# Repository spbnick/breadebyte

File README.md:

Breadebyte
==========

Breadebyte is a breakout board for EBYTE E73-2G4M08S1E module containing
Nordic nRF52833 SoC.

This uses a [shared symbol/footprint
library](https://github.com/spbnick/kicad-lib).

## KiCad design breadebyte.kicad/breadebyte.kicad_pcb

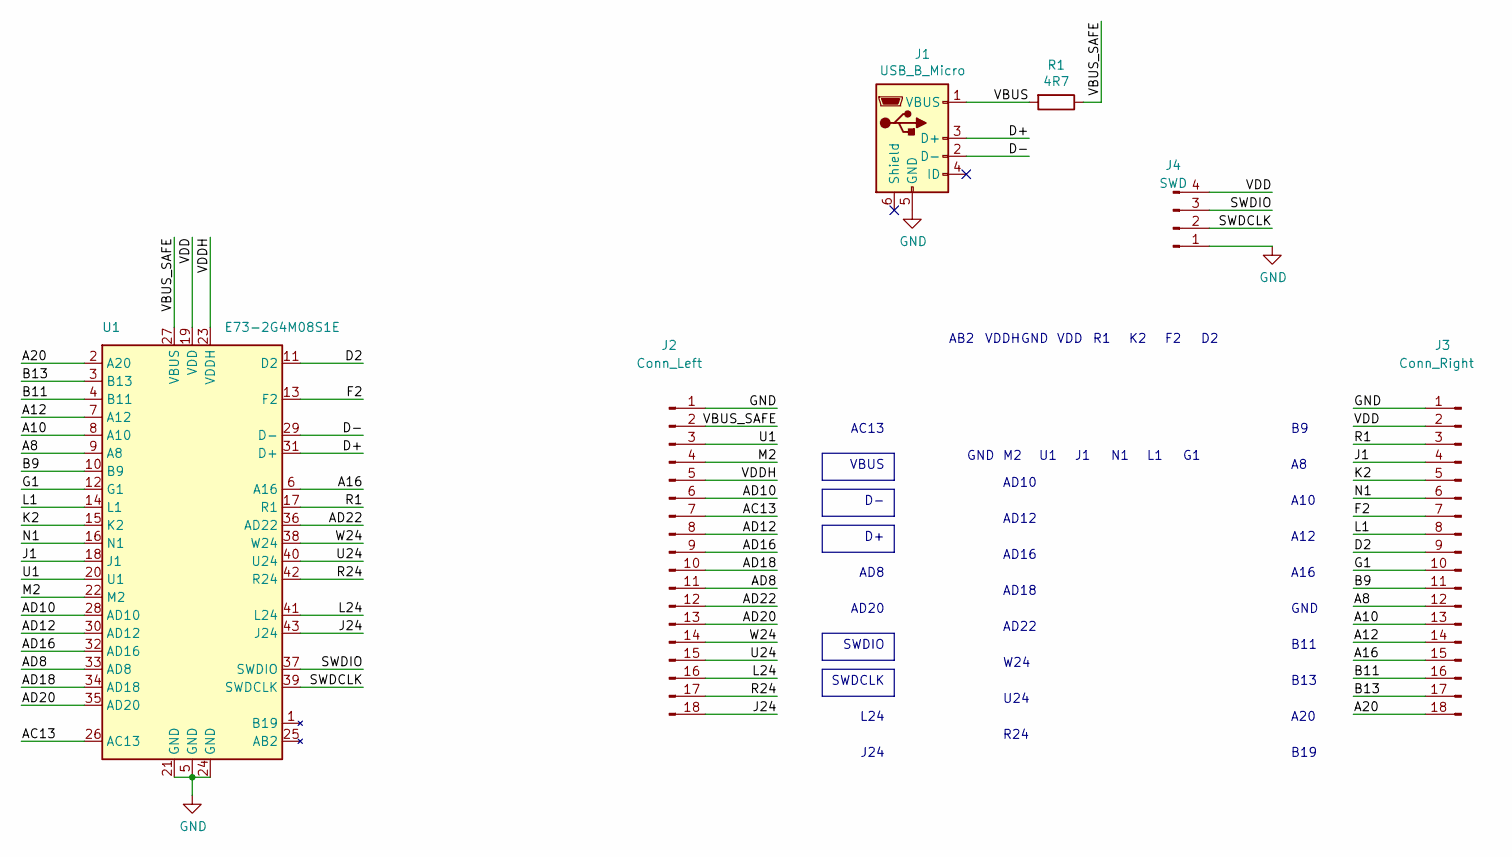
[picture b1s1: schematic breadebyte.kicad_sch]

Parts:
J1: USB_B_Micro; USB_Micro-B_HRO_U-D-M5DD-W-1_Vertical
J2: Conn_Left; PinHeader_1x18_P2.54mm_Vertical
J3: Conn_Right; PinHeader_1x18_P2.54mm_Vertical
J4: SWD; PinHeader_1x04_P2.54mm_Vertical
R1: 4R7; R_0805_2012Metric
U1: E73-2G4M08S1E

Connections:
/A8: J3.12, U1.9 (A8)
/A10: J3.13, U1.8 (A10)
/A12: J3.14, U1.7 (A12)
/A16: J3.15, U1.6 (A16)
/A20: J3.18, U1.2 (A20)
/AC13: J2.7, U1.26 (AC13)
/AD8: J2.11, U1.33 (AD8)
/AD10: J2.6, U1.28 (AD10)
/AD12: J2.8, U1.30 (AD12)
/AD16: J2.9, U1.32 (AD16)
/AD18: J2.10, U1.34 (AD18)
/AD20: J2.13, U1.35 (AD20)
/AD22: J2.12, U1.36 (AD22)
/B9: J3.11, U1.10 (B9)
/B11: J3.16, U1.4 (B11)
/B13: J3.17, U1.3 (B13)
/D2: J3.9, U1.11 (D2)
/D+: J1.3 (D+), U1.31 (D+)
/D-: J1.2 (D-), U1.29 (D-)
/F2: J3.7, U1.13 (F2)
/G1: J3.10, U1.12 (G1)
/J1: J3.4, U1.18 (J1)
/J24: J2.18, U1.43 (J24)
/K2: J3.5, U1.15 (K2)
/L1: J3.8, U1.14 (L1)
/L24: J2.16, U1.41 (L24)
/M2: J2.4, U1.22 (M2)
/N1: J3.6, U1.16 (N1)
/R1: J3.3, U1.17 (R1)
/R24: J2.17, U1.42 (R24)
/SWDCLK: J4.2, U1.39 (SWDCLK)
/SWDIO: J4.3, U1.37 (SWDIO)
/U1: J2.3, U1.20 (U1)
/U24: J2.15, U1.40 (U24)
/VBUS: J1.1 (VBUS), R1.2
/VBUS_SAFE: J2.2, R1.1, U1.27 (VBUS)
/VDD: J3.2, J4.4, U1.19 (VDD)
/VDDH: J2.5, U1.23 (VDDH)
/W24: J2.14, U1.38 (W24)
GND: J1.5 (GND), J2.1, J3.1, J4.1, U1.5 (GND), U1.21 (GND), U1.24 (GND)

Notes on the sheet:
B19
AB2
R24
AD22
VBUS
B13
A10
AD18
U24
GND
J24
SWDIO
L24
VDDH
SWDCLK
AD10
B11
AD12
AD8
A12
A20
A16
AD16
VDD
W24
AD20
AC13

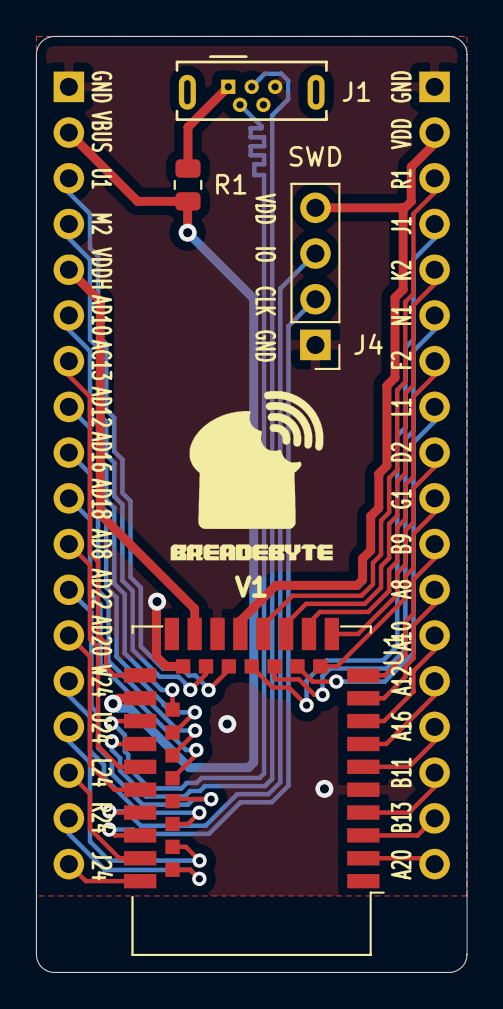
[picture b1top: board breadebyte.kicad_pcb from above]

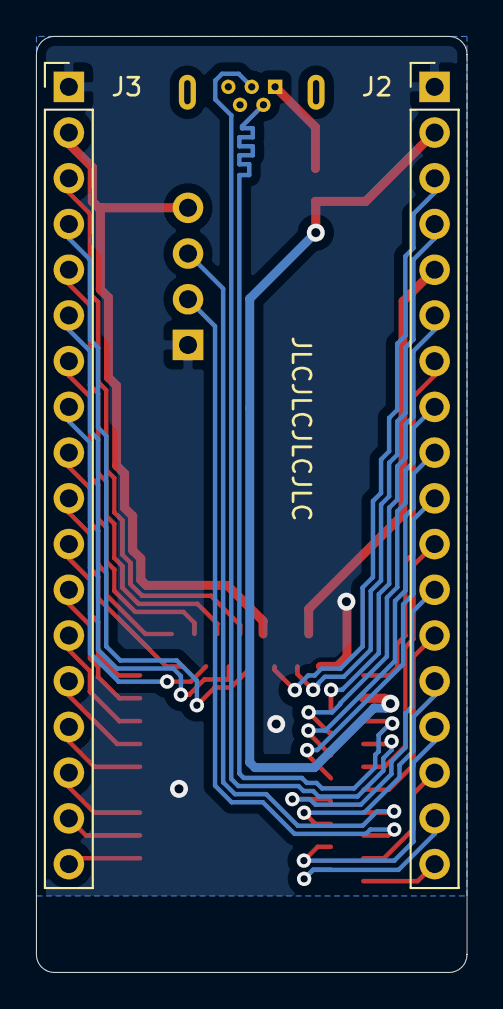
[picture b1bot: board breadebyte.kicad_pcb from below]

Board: 2 copper layers, 23.9 x 52.0 mm, 7 parts (2 on the bottom side), 40 nets.

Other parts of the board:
Ref**: Val**; logo

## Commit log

2022-01-22 Add v1 design
2022-01-22 Add a README.md with a photo
2022-04-23 Upgrade KiCAD project to KiCAD v6
2022-05-14 Switch to using shared symbol/footprint library
